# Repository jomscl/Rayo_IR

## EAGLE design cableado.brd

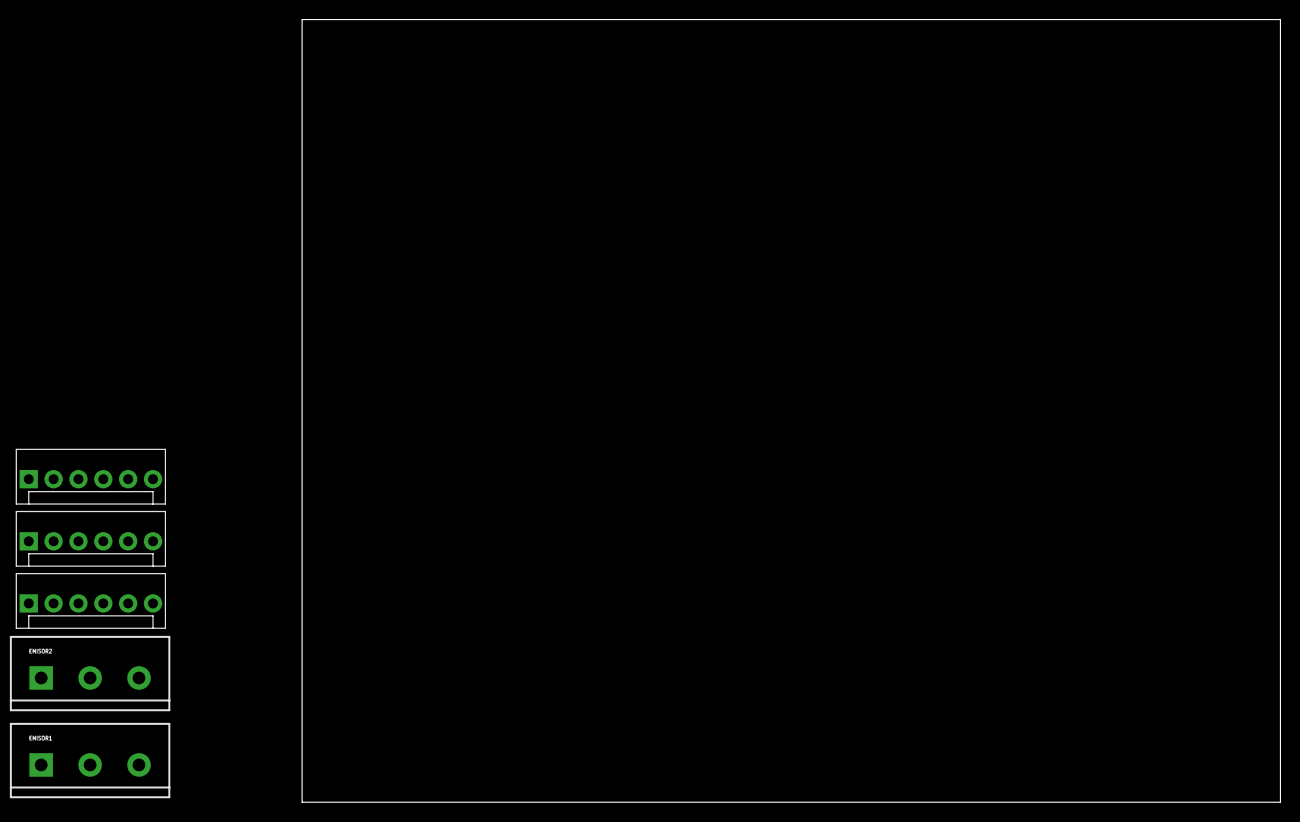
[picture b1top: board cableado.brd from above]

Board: 2 copper layers, 100.0 x 80.0 mm, 5 parts (0 on the bottom side), 5 nets, no tracks yet.

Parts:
EMISOR1, EMISOR2: SCREWTERMINAL-5MM-3
MOTOR: MOLEX-1X6
RECEPTOR1, RECEPTOR2: MOLEX-1X6

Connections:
24VAC: EMISOR1.3, EMISOR2.3, MOTOR.3, RECEPTOR1.6, RECEPTOR2.6
COMUN2: RECEPTOR1.2, RECEPTOR2.4
GND: MOTOR.5, RECEPTOR2.2
GNDAC: EMISOR1.1, EMISOR2.1, MOTOR.2, RECEPTOR1.5, RECEPTOR2.5
SEGURIDAD: MOTOR.6, RECEPTOR1.4

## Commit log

2014-10-27 :tada: Added .gitattributes & .gitignore files
2014-10-27 Subida inicial
2014-10-27 Desarrollo 2
2014-10-27 Desarrollo fin?
2014-10-29 Eagle1
2014-10-29 Eagle fail
2014-11-04 Debug 1
2014-11-05 Debug 2

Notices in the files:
parts and their libraries:
SparkFun-Connectors: Licensing: Creative Commons ShareAlike 4.0 International - https://creativecommons.org/licenses/by-sa/4.0
